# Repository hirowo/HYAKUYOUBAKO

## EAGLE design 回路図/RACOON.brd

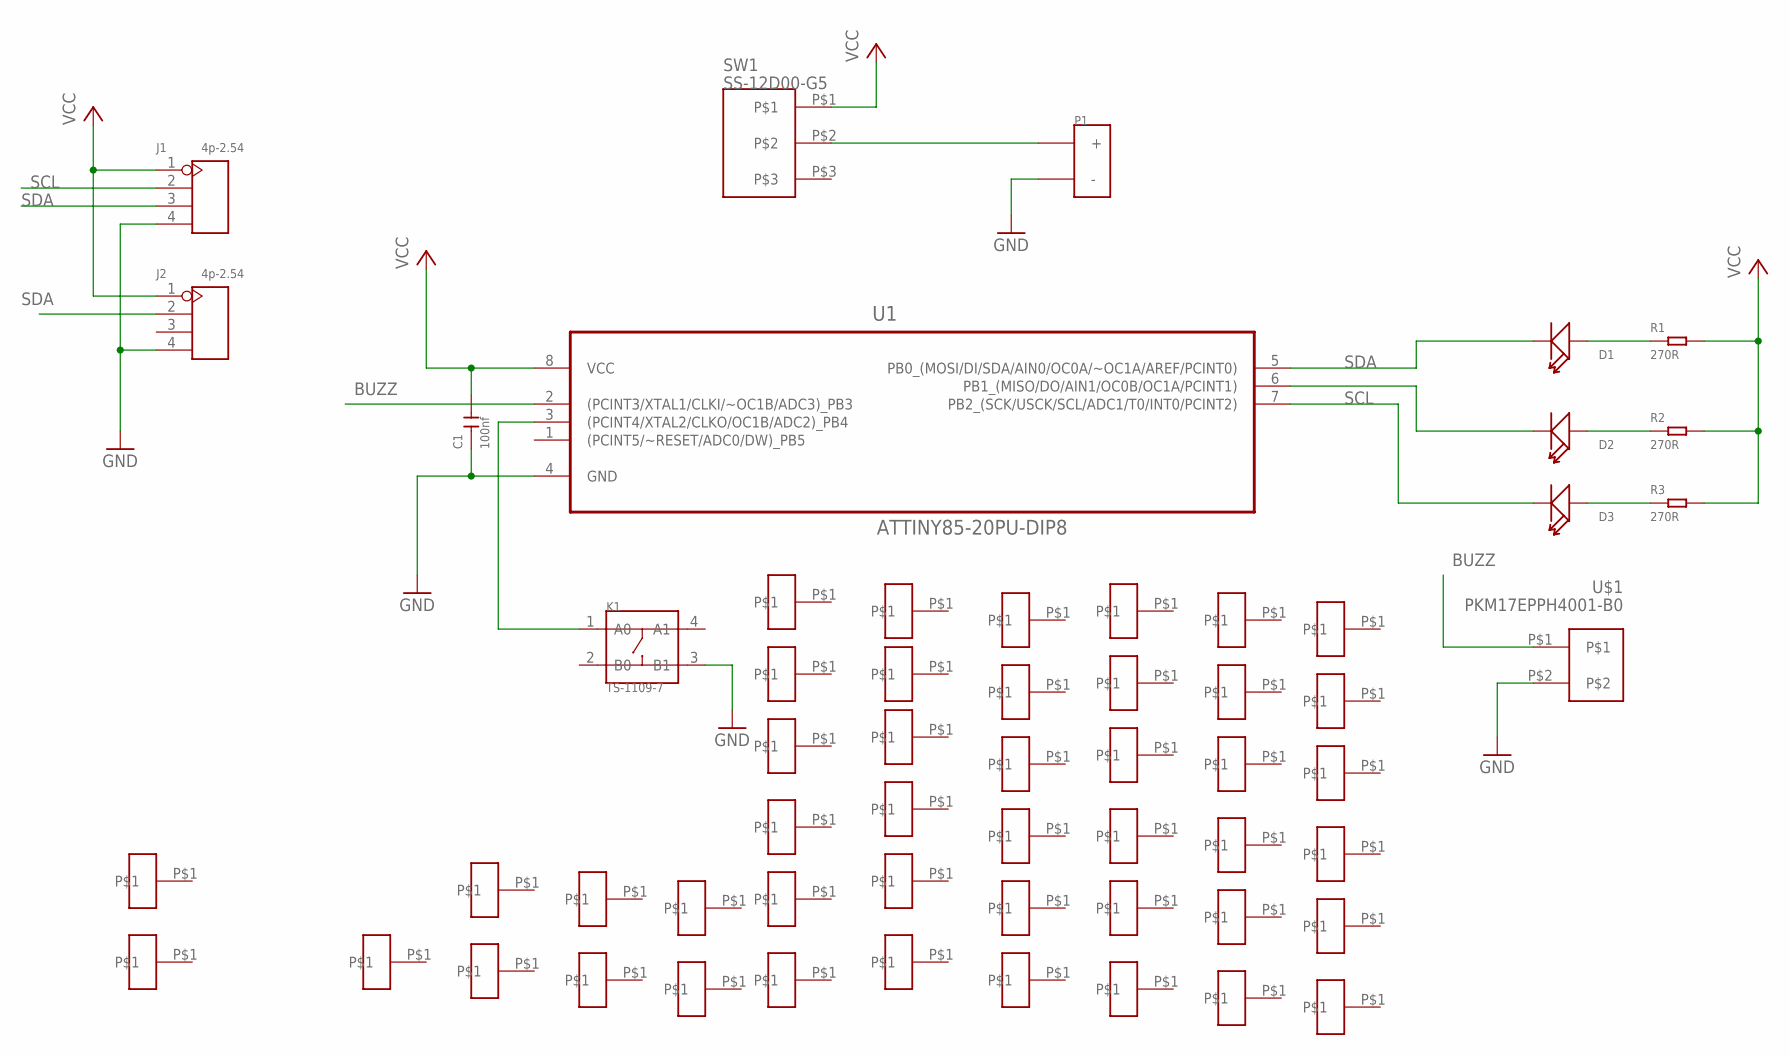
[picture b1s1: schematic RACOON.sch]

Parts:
C1: 100nf; CERAMIC-2.54
D1, D2, D3: 504BW; LED2-2.54-D5.0MM
J1, J2: 4p-2.54; H4-2.54
K1: TS-1109-7; SW4-6.2X6.2X5.0MM
P1: BATTERY; BAT_CR2450_TH_BS2450
R1, R2, R3: 270R; PR-D2.3XL6.5MM
SW1: SS-12D00-G5
U1: ATTINY85-20PU-DIP8; DIP254P762X533-8
U$1: PKM17EPPH4001-B0
U$2, U$3, U$4, U$5, U$6, U$7, U$8, U$9, U$10, U$11, U$12, U$13, U$14, U$15, U$16, U$17, U$18, U$19, U$20, U$21, U$22, U$23, U$24, U$25, U$26, U$27, U$28, U$29, U$30, U$31, U$32, U$33, U$34, U$35, U$36, U$37, U$41, U$42, U$43, U$44, U$45, U$46, U$47, U$49, U$50: 1PIN_HOLE

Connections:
BUZZ: U1.2 ((PCINT3/XTAL1/CLKI/~OC1B/ADC3)_PB3), U$1.P$1
GND: C1.1, J1.4, J2.4, K1.3 (B1), P1.-, U1.4 (GND), U$1.P$2
unnamed: D1.+, R1.1
unnamed: P1.+, SW1.P$2
unnamed: D2.+, R2.1
unnamed: K1.1 (A0), U1.3 ((PCINT4/XTAL2/CLKO/OC1B/ADC2)_PB4)
unnamed: D3.+, R3.1
unnamed: D2.-, U1.6 (PB1_(MISO/DO/AIN1/OC0B/OC1A/PCINT1))
SCL: D3.-, J1.2, U1.7 (PB2_(SCK/USCK/SCL/ADC1/T0/INT0/PCINT2))
SDA: D1.-, J1.3, J2.2, U1.5 (PB0_(MOSI/DI/SDA/AIN0/OC0A/~OC1A/AREF/P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)
VCC: C1.2, J1.1, J2.1, R1.2, R2.2, R3.2, SW1.P$1, U1.8 (VCC)

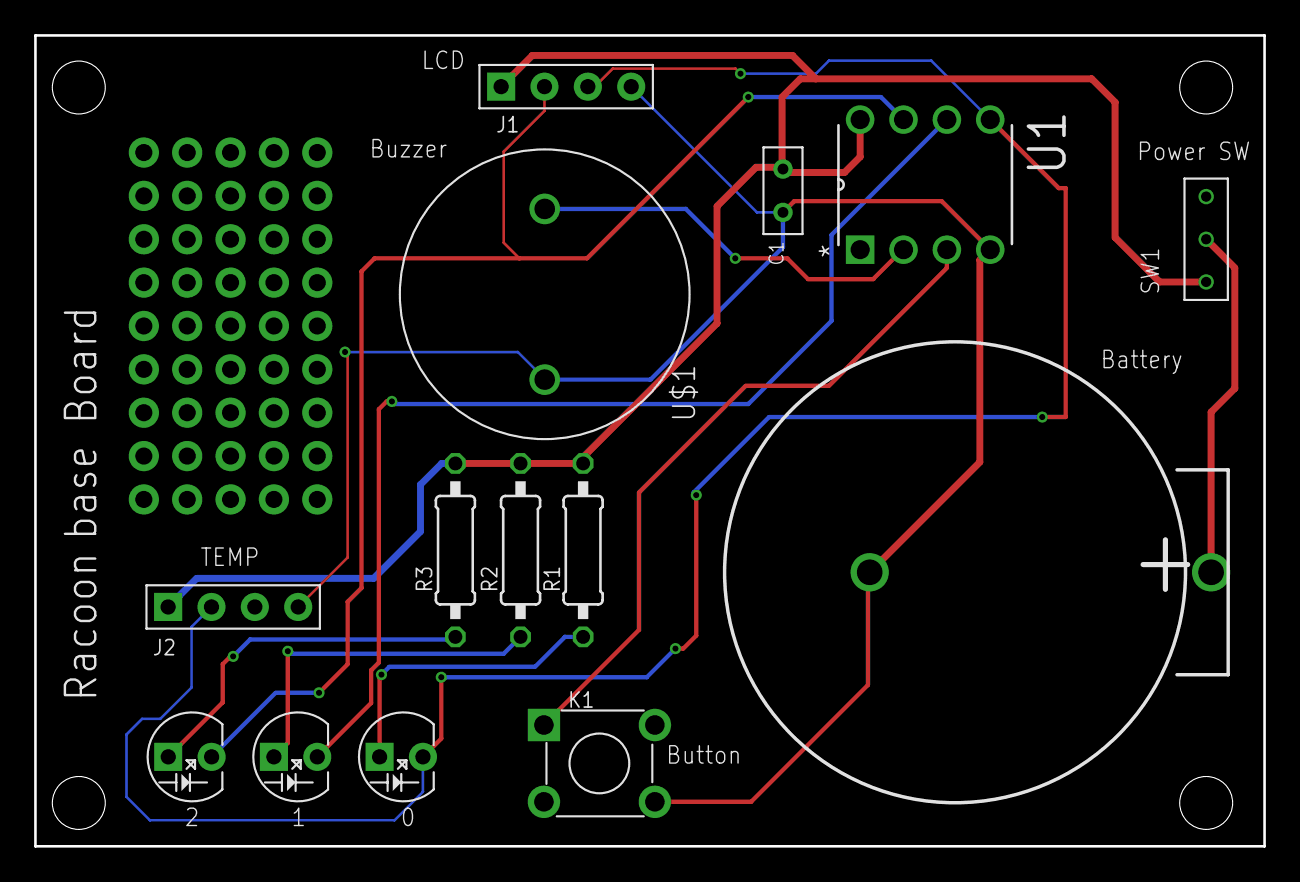
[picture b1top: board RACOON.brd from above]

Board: 2 copper layers, 72.0 x 47.5 mm, 59 parts (0 on the bottom side), 11 nets.

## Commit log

2020-08-01 初版
    百葉箱初版
    attiny85用
2020-08-01 回路図をアップ
